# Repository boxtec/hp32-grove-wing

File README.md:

HelvePic32 Grove Wing Kit

See http://helvepic32.net or http://helvepic32.org/ for more information.

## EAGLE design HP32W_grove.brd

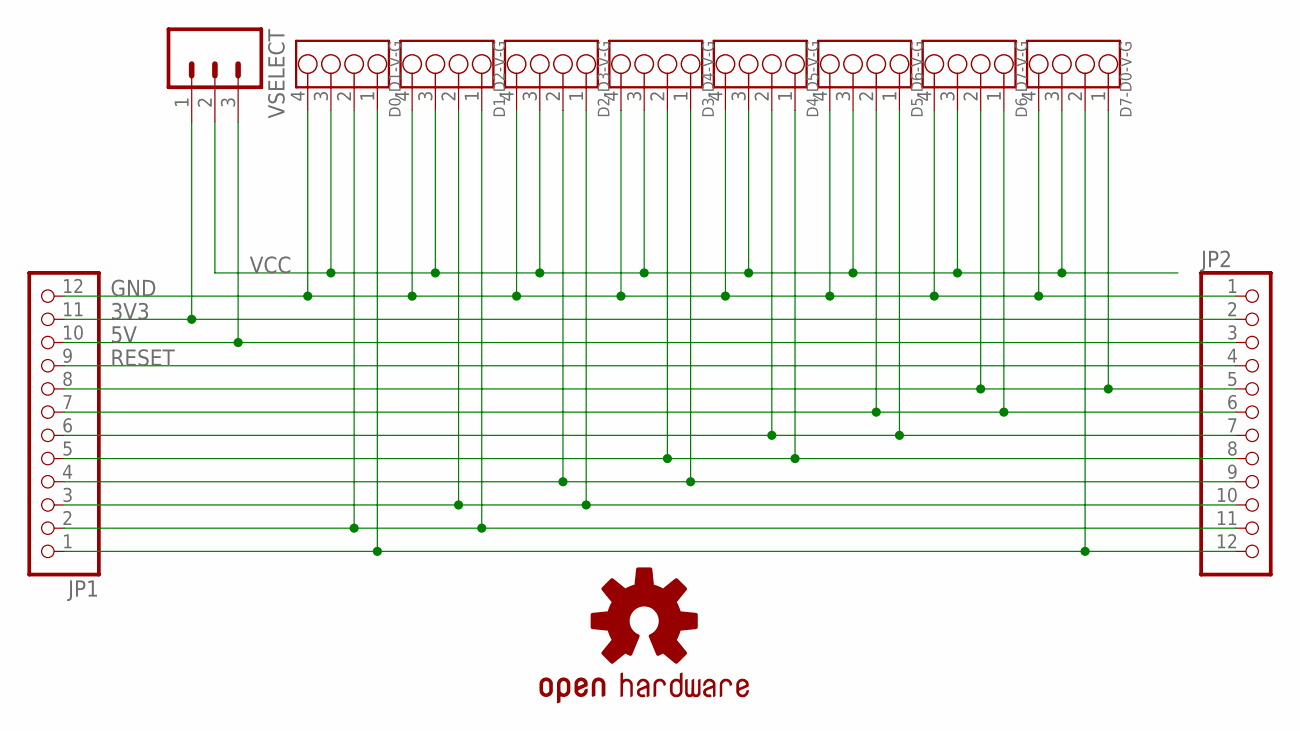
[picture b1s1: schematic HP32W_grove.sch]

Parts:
D0-D1-V-G, D1-D2-V-G, D2-D3-V-G, D3-D4-V-G, D4-D5-V-G, D5-D6-V-G, D6-D7-V-G, D7-D0-V-G: GROVE-4P-2.0-3470130P1; 4P-2.0
JP1, JP2: PINHD-1X12-CB; 1X12-CB
LOGO1: OSHW-LOGOS; OSHW-LOGO-S
VSELECT: M03PTH; 1X03

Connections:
3V3: JP1.11, JP2.2, VSELECT.1
5V: JP1.10, JP2.3, VSELECT.3
GND: D0-D1-V-G.4, D1-D2-V-G.4, D2-D3-V-G.4, D3-D4-V-G.4, D4-D5-V-G.4, D5-D6-V-G.4, D6-D7-V-G.4, D7-D0-V-G.4, JP1.12, JP2.1
unnamed: D6-D7-V-G.2, D7-D0-V-G.1, JP1.8, JP2.5
unnamed: D5-D6-V-G.2, D6-D7-V-G.1, JP1.7, JP2.6
unnamed: D4-D5-V-G.2, D5-D6-V-G.1, JP1.6, JP2.7
unnamed: D3-D4-V-G.2, D4-D5-V-G.1, JP1.5, JP2.8
unnamed: D2-D3-V-G.2, D3-D4-V-G.1, JP1.4, JP2.9
unnamed: D1-D2-V-G.2, D2-D3-V-G.1, JP1.3, JP2.10
unnamed: D0-D1-V-G.2, D1-D2-V-G.1, JP1.2, JP2.11
unnamed: D0-D1-V-G.1, D7-D0-V-G.2, JP1.1, JP2.12
RESET: JP1.9, JP2.4
VCC: D0-D1-V-G.3, D1-D2-V-G.3, D2-D3-V-G.3, D3-D4-V-G.3, D4-D5-V-G.3, D5-D6-V-G.3, D6-D7-V-G.3, D7-D0-V-G.3, VSELECT.2

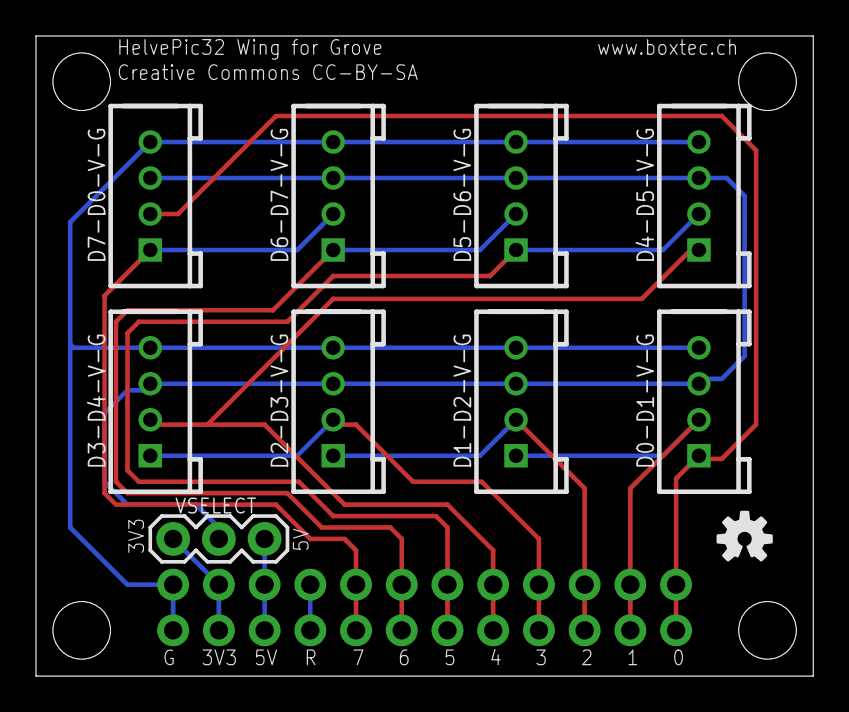
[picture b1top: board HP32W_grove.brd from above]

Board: 2 copper layers, 43.2 x 35.6 mm, 12 parts (0 on the bottom side), 13 nets.

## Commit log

2015-09-10 Initial github import

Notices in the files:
HP32W_grove.brd:
Creative Commons CC-BY-SA
parts and their libraries:
SparkFun-Connectors: Licensing: Creative Commons ShareAlike 4.0 International - https://creativecommons.org/licenses/by-sa/4.0
